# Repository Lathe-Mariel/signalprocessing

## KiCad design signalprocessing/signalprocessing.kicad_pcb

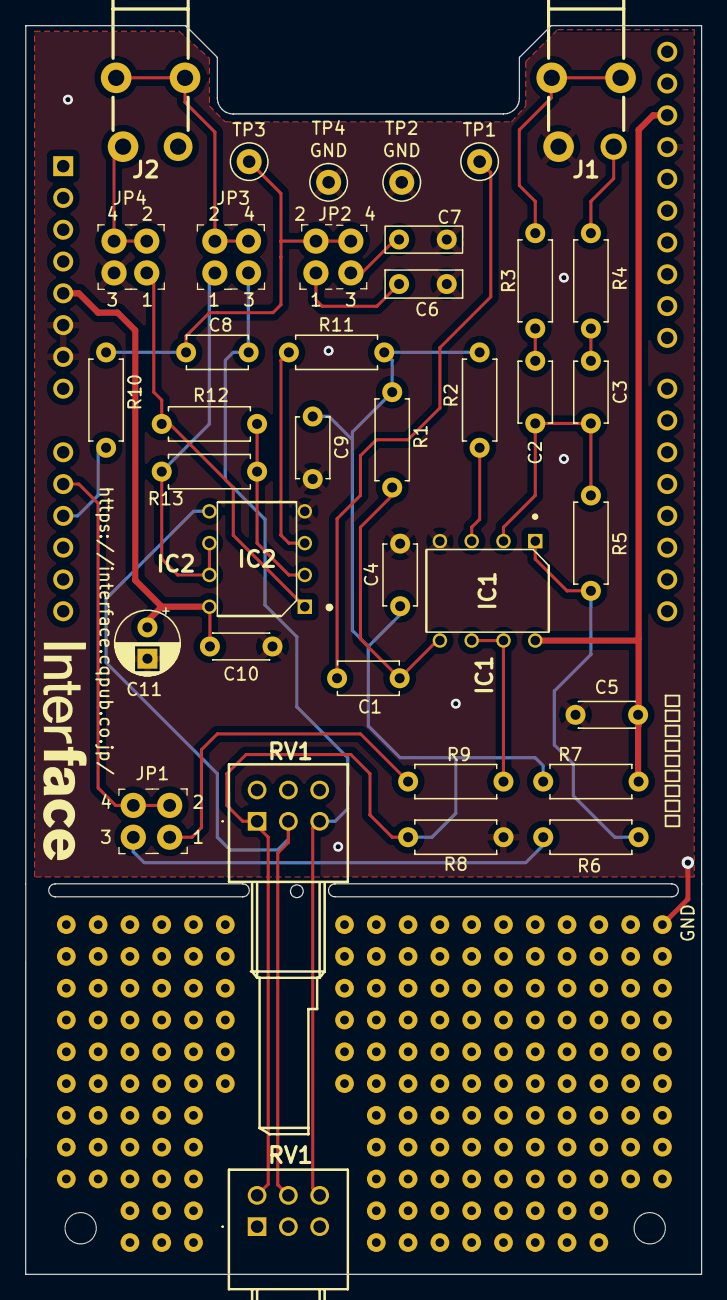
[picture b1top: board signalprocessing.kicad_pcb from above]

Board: 2 copper layers, 54.0 x 99.8 mm, 43 parts (0 on the bottom side), 29 nets.

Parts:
C1, C2, C3, C4, C8, C9: 1μ; C_Disc_D4.7mm_W2.5mm_P5.00mm
C5, C10: 0.1μ; C_Disc_D4.3mm_W1.9mm_P5.00mm
C6: 0.0047μ(mila); C_Rect_L7.0mm_W2.0mm_P5.00mm
C7: 0.001μ(mila); C_Rect_L7.0mm_W3.5mm_P5.00mm
C11: 100μ; CP_Radial_D5.0mm_P2.50mm
IC1: MCP6022-I_P; DIP794W56P254L946H432Q8N
IC2: NJU7043D; DIP762W56P254L880H425Q8N
J1, J2: MJ-8435
JP1, JP2, JP3, JP4, JP11, JP12, JP13, JP14: 22-23-2021; PinHeader_1x2_P2.54mm_Drill1.02mm
R1, R2, R5, R11, R12, R13: 100k; R_Axial_DIN0207_L6.3mm_D2.5mm_P7.62mm_Horizontal
R3, R4: 47k; R_Axial_DIN0207_L6.3mm_D2.5mm_P7.62mm_Horizontal
R6, R9: 22; R_Axial_DIN0207_L6.3mm_D2.5mm_P7.62mm_Horizontal
R7, R8: 220k; R_Axial_DIN0207_L6.3mm_D2.5mm_P7.62mm_Horizontal
R10: 6.8k; R_Axial_DIN0207_L6.3mm_D2.5mm_P7.62mm_Horizontal
RV1, RV1#2: R_Potentiometer; RK09712200HA
TP1: 入力; TestPoint_Loop_D2.50mm_Drill1.0mm
TP2, TP4: TestPoint; TestPoint_Loop_D2.50mm_Drill1.0mm
TP3: 出力; TestPoint_Loop_D2.50mm_Drill1.0mm
U1: Nucleo64-F446; Arduino_header

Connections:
+5V: C10.2, C11.1, IC2.8 (VDD_(V+)), U1.5 (+5V)
/R11: C4.2, C9.2, R1.2, R2.1, R7.2, R8.1, R11.1, RV1.R11 (1), RV1.R21, RV1#2.R11 (1)
/R13: C8.2, JP3.1, RV1.R13 (3), RV1.R23, RV1#2.R13 (3)
GND: C4.1, C5.1, C6.2, C7.2, C9.1, C10.1, C11.2, IC1.4 (VSS), IC2.4 (VSS_(V-)), J1.1 (GND), JP14.2, R8.2, TP2.1, TP4.1, U1.6 (GND), U1.7 (GND), U1.29 (GND)
unnamed: C1.1, IC1.5 (VINB+), R1.1
unnamed: C1.2, TP1.1
unnamed: C2.1, R3.2
unnamed: C2.2, C3.2, IC1.2 (VINA-), R5.1
unnamed: C3.1, R4.2
unnamed: C6.1, JP2.1
unnamed: C7.1, JP12.1
unnamed: C8.1, JP2.2, JP12.2, R10.2, TP3.1
unnamed: IC1.1 (VOUTA), R5.2, R6.2
unnamed: IC1.3 (VINA+), R2.2
unnamed: IC1.6 (VINB-), IC1.7 (VOUTB), R9.1
unnamed: IC2.1 (OUTPUT_A), JP4.1, R12.1
unnamed: IC2.2 (-INPUT_A), R12.2, R13.2
unnamed: IC2.3 (+INPUT_A), R11.2
unnamed: IC2.5 (+INPUT_B), RV1.R12 (2), RV1.R22, RV1#2.R12 (2)
unnamed: IC2.6 (-INPUT_B), IC2.7 (OUTPUT_B), JP13.2, R13.1
unnamed: J1.2 (L), J1.3 (L), R3.1
unnamed: J1.4 (R), R4.1
unnamed: J2.1 (GND), JP4.2, JP14.1
unnamed: J2.2 (L), J2.3 (L), JP3.2, JP13.1
unnamed: JP1.1, R9.2
unnamed: JP1.2, JP11.1, U1.10 (PA1(A1))
unnamed: JP11.2, R6.1
unnamed: R10.1, U1.11 (PA4(A2))
VDDA: C5.2, IC1.8 (VDD), R7.1, U1.30 (AVDD)

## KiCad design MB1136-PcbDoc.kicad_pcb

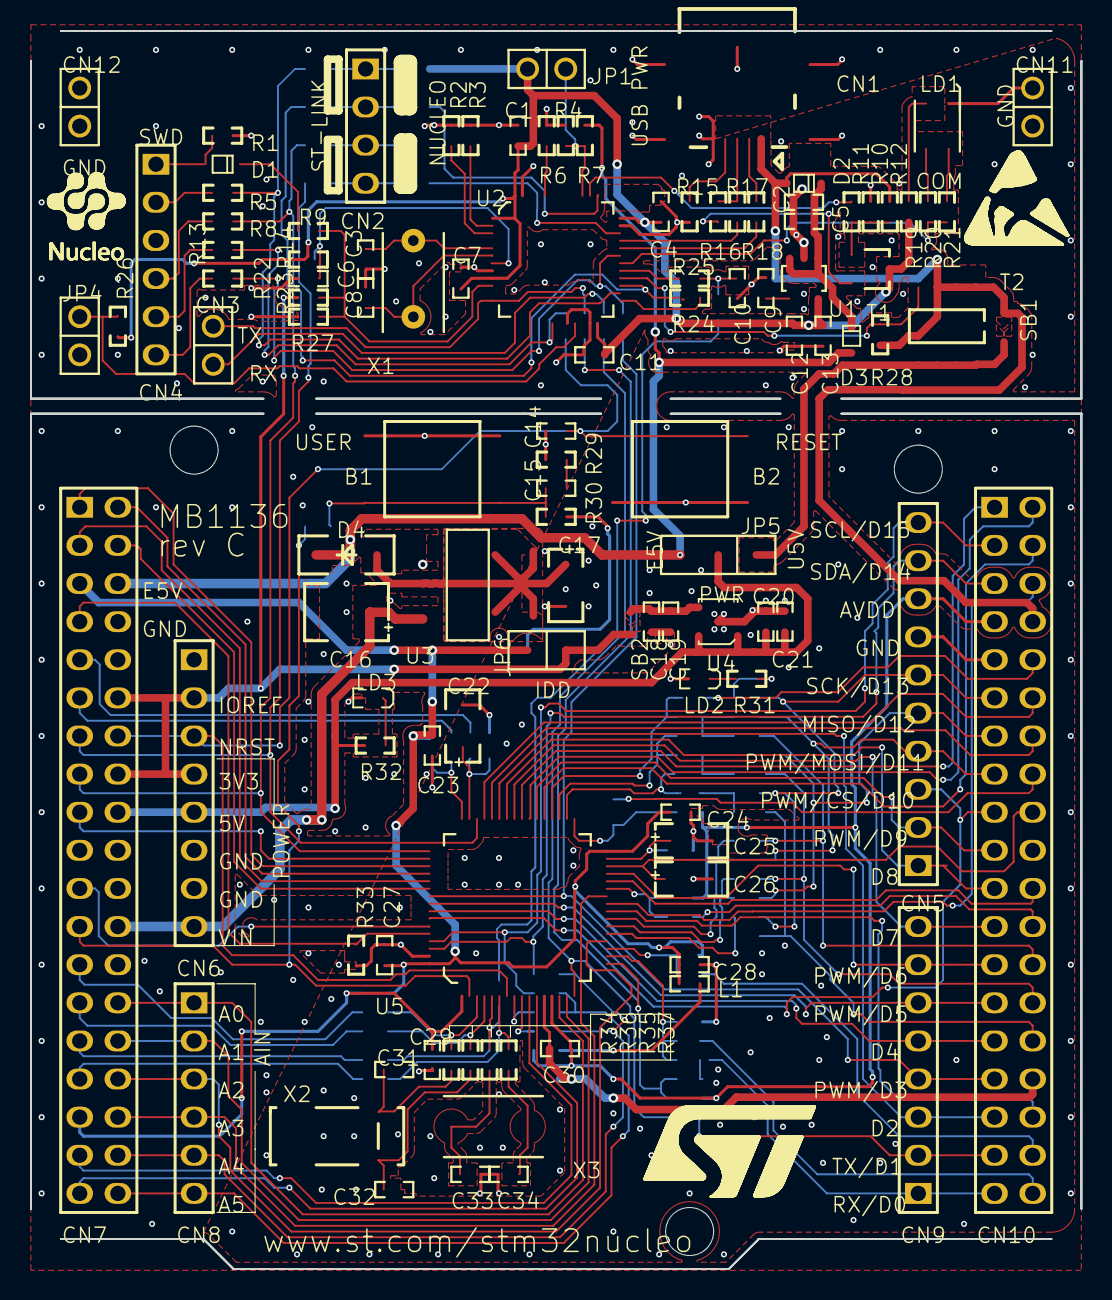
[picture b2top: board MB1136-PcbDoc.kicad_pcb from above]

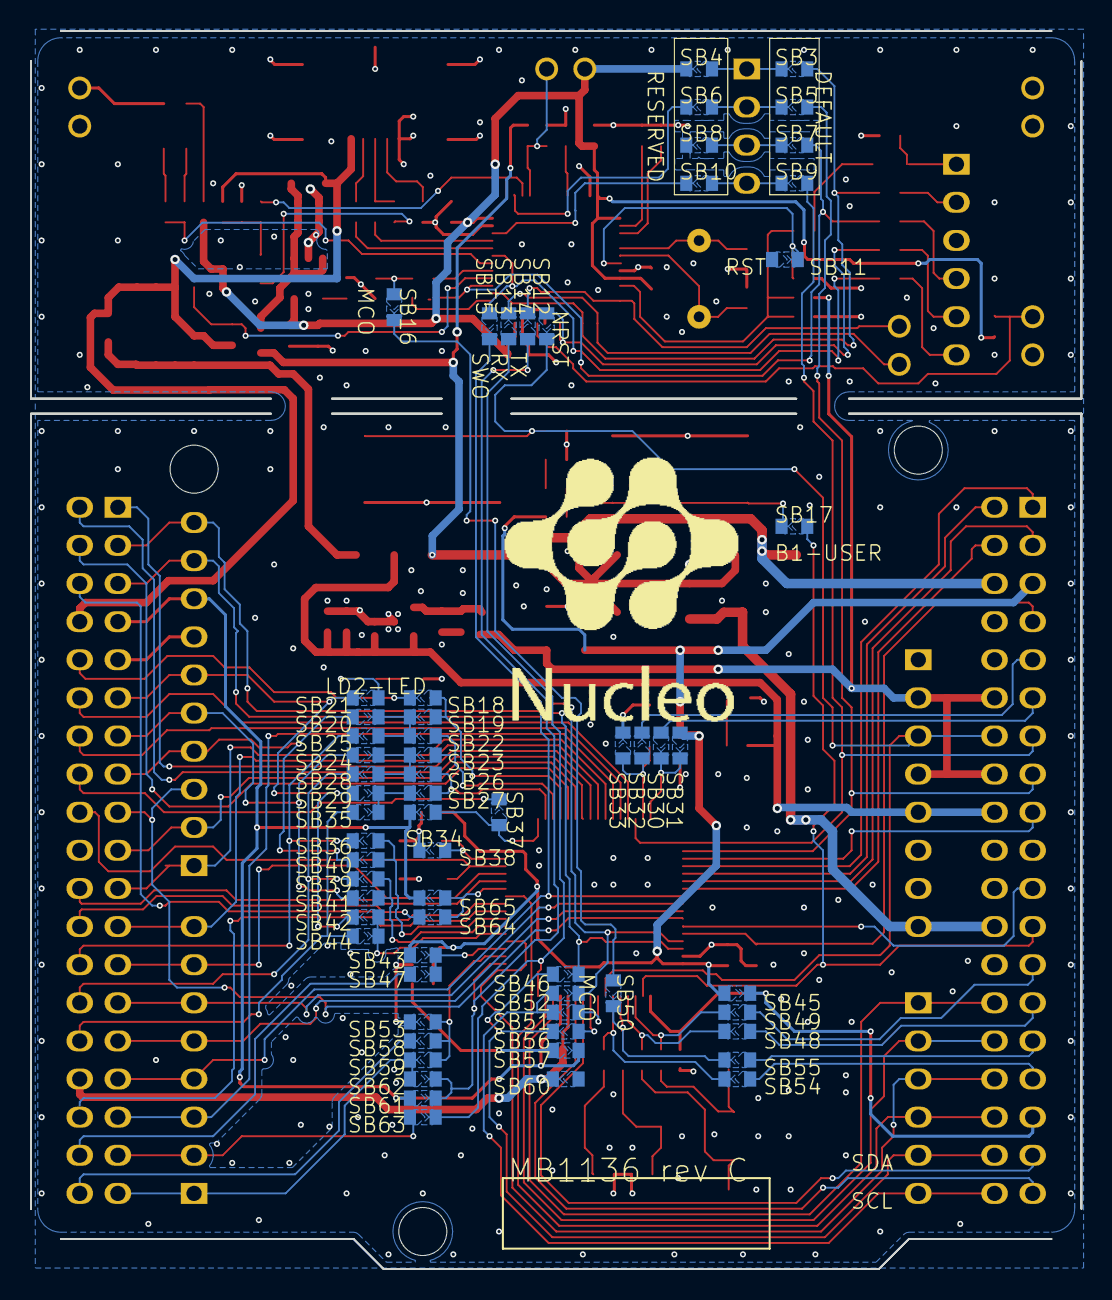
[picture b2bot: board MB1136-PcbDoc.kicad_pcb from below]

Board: 2 copper layers, 70.0 x 82.5 mm, 77 parts (63 on the bottom side), 74 nets.

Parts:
CN1: Header, 6-Pin, Single row; 1*6P
CN2: Header, 4-Pin, Single row; 1*4
CN4, CN11#2, CN12: SIP2_2.54
CN5: Header, 10-Pin, Single row,female; 1*10P_FEMALE
CN8, CN11: Header, 8-Pin, Single row,female; 1*8P_FEMALE
CN9, CN10: Header, 19-Pin, Dual row; 2*19P
CN14: Header, 6-Pin, Single row,female; 1*6P_FEMALE
JP4, JP6: SIP2_2.54
SB1, SB2, SB3, SB4, SB5, SB6, SB7, SB8, SB9, SB10, SB11, SB12, SB13, SB14, SB15, SB16, SB17, SB18, SB19, SB20, SB21, SB22, SB23, SB24, SB25, SB26, SB27, SB28, SB29, SB30, SB31, SB32, SB33, SB34, SB35, SB36, SB37, SB38, SB39, SB40, SB41, SB42, SB43, SB44, SB47, SB48, SB49, SB50, SB51, SB52, SB53, SB54, SB55, SB56, SB57, SB58, SB59, SB60, SB61, SB62, SB63, SB64, SB65: Circuit Breaker; JP2_SMD
X1: Crystal Oscillator; XTAL1

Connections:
+3V3: CN8.2, CN8.4, CN9.12, CN9.16
+3V3_ST_LINK: JP4.1, SB4.2
+5V: CN8.5, CN9.18
AGND: CN10.32, SB43.2
AVDD: CN5.8, CN10.7, SB16.1, SB17.2, SB42.2, SB65.2
GND: CN1.3, CN5.7, CN8.6, CN8.7, CN9.8, CN9.19, CN9.20, CN9.22, CN10.9, CN10.20, CN11#2.1, CN11#2.2, CN12.1, CN12.2, JP6.1, SB8.2, SB11.1, SB27.2, SB31.2, SB36.2, SB43.1
MCO: SB20.1, SB51.2
NRST: CN8.3, CN9.14, SB1.2
NetC22_1: SB31.1, SB33.1
NetCN2_1: CN2.1, SB3.2, SB4.1
NetCN2_2: CN2.2, SB5.2, SB6.1
NetCN2_3: CN2.3, SB7.2, SB8.1
NetCN2_4: CN2.4, SB9.2, SB10.1
NetCN5_4: CN5.4, CN10.15, SB60.2, SB61.1
NetCN5_5: CN5.5, CN10.13, SB57.2, SB58.1
NetCN5_6: CN5.6, CN10.11, SB41.2, SB53.2, SB54.1
NetCN7_25: CN9.25, SB37.1
NetCN7_27: CN9.27, SB38.1
NetCN7_29: CN9.29, SB39.1
NetCN7_31: CN9.31, SB40.1
NetCN7_36: CN9.36, CN14.5, SB47.2, SB50.1
NetCN7_38: CN9.38, CN14.6, SB48.1, SB49.2
NetCN10_26: CN10.26, SB52.2, SB55.2
NetCN10_28: CN10.28, SB62.2, SB63.2
NetCN10_30: CN10.30, SB56.1, SB59.1
NetSB13_1: SB13.1, SB14.2
NetSB14_1: SB12.1, SB15.2, SB16.2
NetSB18_1: SB25.1, SB26.1
NetSB22_1: SB23.1, SB24.1
NetSB26_1: SB18.1, SB22.1
NetSB30_2: SB28.2, SB30.2
NetSB34_1: SB17.1, SB44.1
NetSB43_2: SB29.2, SB32.2
NetSB53_1: SB34.1, SB35.1, SB36.1
NetSB64_1: SB64.1, SB65.1
PA0: CN9.28, CN14.1
PA1: CN9.30, CN14.2
PA2: CN10.35, CN11.2, SB14.1
PA3: CN10.37, CN11.1, SB15.1, SB34.2
PA4: CN9.32, CN14.3
PA5: SB53.1, SB59.2
PA6: SB57.1, SB63.1
PA7: SB55.1, SB60.1
PA8: CN10.23, CN11.8
PA9: CN5.1, CN10.21
PA10: CN10.33, CN11.3
PA13: CN9.13, SB9.1
PA14: CN9.15, SB5.1
PB0: CN9.34, CN14.4
PB1: CN10.24, SB64.2
PB3: CN10.31, CN11.4, SB2.2
PB4: CN10.27, CN11.6
PB5: CN10.29, CN11.5
PB6: CN5.3, CN10.17
PB8: CN5.10, CN10.3, SB48.2
PB9: CN5.9, CN10.5, SB50.2
PB10: CN10.25, CN11.7
PB12: CN10.16, SB44.2
PB13: SB18.2, SB54.2, SB56.2
PB14: SB22.2, SB23.2, SB58.2, SB62.1
PB15: SB24.2, SB25.2, SB52.1, SB61.2
PC7: CN5.2, CN10.19
PC13: CN9.23, SB19.1
PD8: CN10.10, SB26.2
PF0: SB20.2, SB39.2
PF4: CN10.38, SB35.2
PF5: CN10.36, SB32.1
PF6: CN9.9, SB33.2
PF7: CN9.11, SB30.1
STLINK_RX: CN4.1, SB13.2
STLINK_TX: CN4.2, SB12.2
VBAT/VLCD: CN9.33, SB21.2
VDD: CN9.5, SB21.1, SB28.1, SB29.1
VIN: CN8.8, CN9.24
